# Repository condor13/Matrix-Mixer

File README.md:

# Matrix-Mixer rev.02 - IN PRODUCTION!

Welcome to the Matrix-Mixer wiki! Matrix mixer is a device that routes multiple input audio signals to multiple outputs.
It employs level controls to determine how much of each input is going to each output. The number of individual controls 
is the number of inputs witch is six multiplied by the number of outputs witch is six so (complex math) 36 controls.
It outputs mono, converts synth level signals to pro line level (+4dBu). LED`s for input clipping.

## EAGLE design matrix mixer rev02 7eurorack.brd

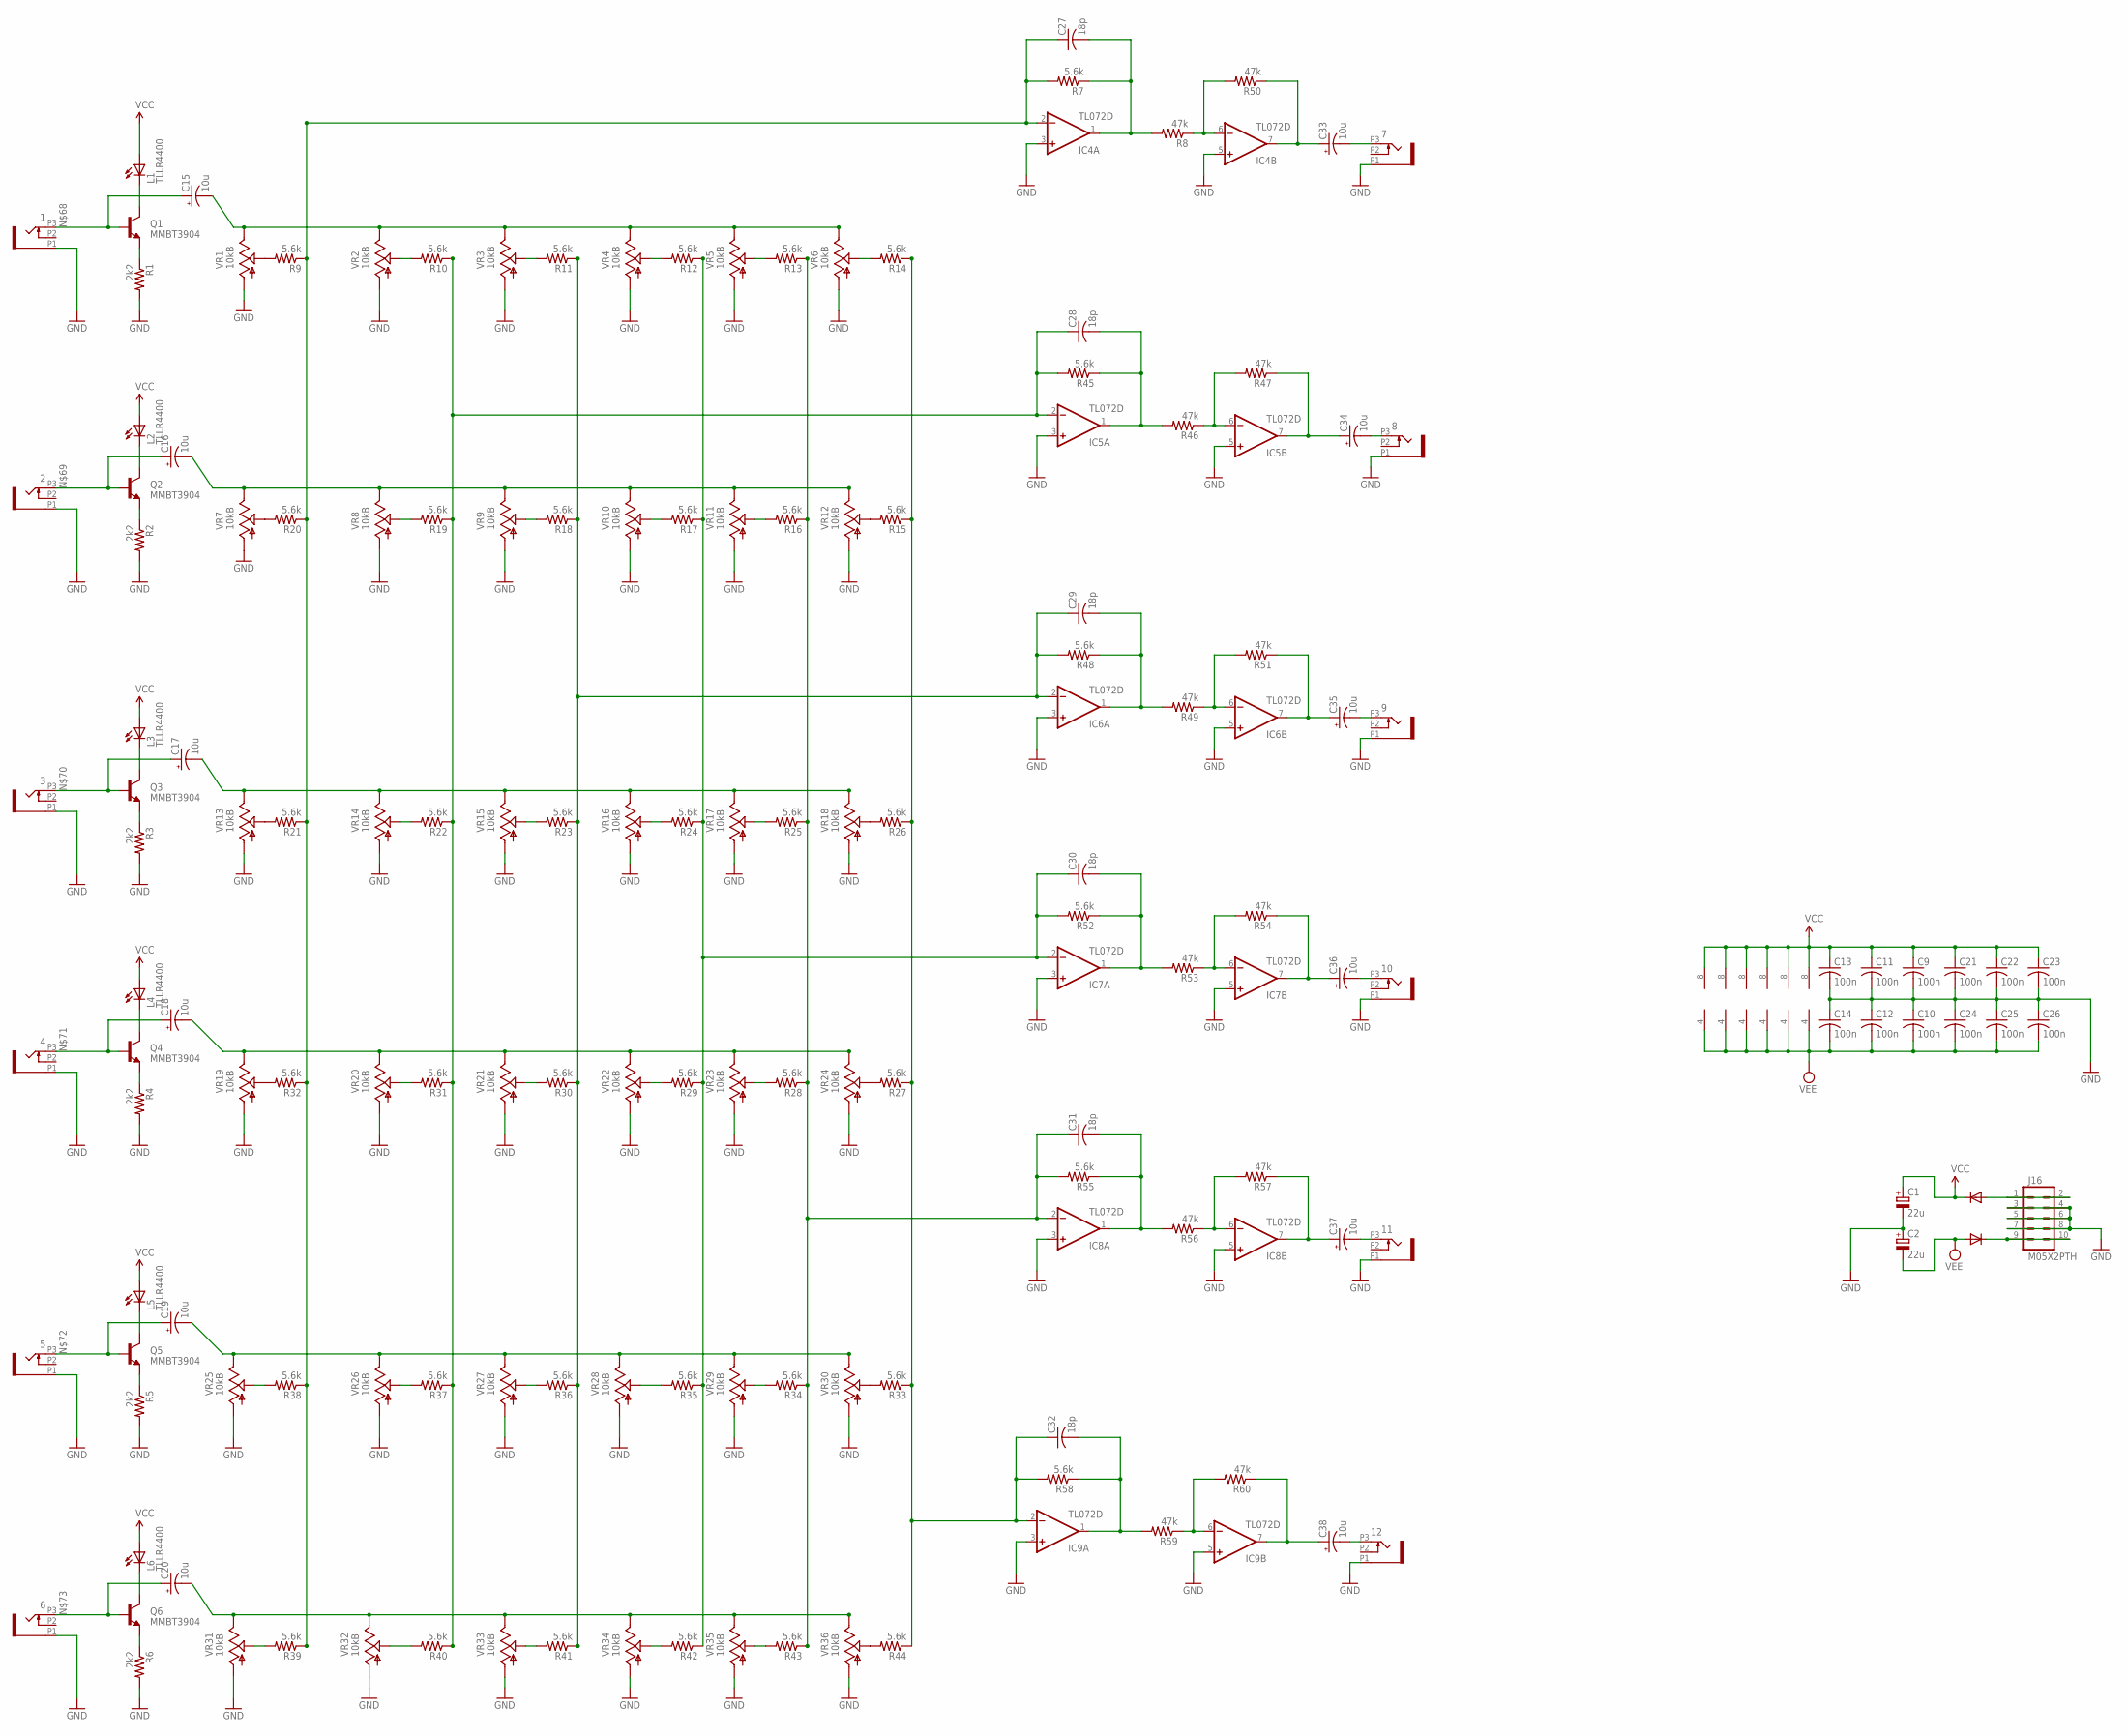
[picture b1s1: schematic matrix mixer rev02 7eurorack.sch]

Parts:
1, 2, 3, 4, 5, 6, 7, 8, 9, 10, 11, 12: PJ301_THONKICONN6; WQP_PJ_301M6
C1, C2: 22u; PANASONIC_D
C9, C10, C11, C12, C13, C14, C21, C22, C23, C24, C25, C26: 100n; C0603
C15, C16, C17, C18, C19, C20, C33, C34, C35, C36, C37, C38: 10u; PANASONIC_B
C27, C28, C29, C30, C31, C32: 18p; C0603
D1, D2: 1N5819HW; SOD123
IC4, IC5, IC6, IC7, IC8, IC9: TL072D; SO08
J16: M05X2PTH; AVR_ICSP
L1, L2, L3, L4, L5, L6: TLLR4400; LED3MM
Q1, Q2, Q3, Q4, Q5, Q6: MMBT3904; SOT23-BEC
R1, R2, R3, R4, R5, R6: 2k2; R0603
R7, R9, R10, R11, R12, R13, R14, R15, R16, R17, R18, R19, R20, R21, R22, R23, R24, R25, R26, R27, R28, R29, R30, R31, R32, R33, R34, R35, R36, R37, R38, R39, R40, R41, R42, R43, R44, R45, R48, R52, R55, R58: 5.6k; R0603
R8, R46, R47, R49, R50, R51, R53, R54, R56, R57, R59, R60: 47k; R0603
VR1, VR2, VR3, VR4, VR5, VR6, VR7, VR8, VR9, VR10, VR11, VR12, VR13, VR14, VR15, VR16, VR17, VR18, VR19, VR20, VR21, VR22, VR23, VR24, VR25, VR26, VR27, VR28, VR29, VR30, VR31, VR32, VR33, VR34, VR35, VR36: 10kB; ALPS_POT_VERTICAL_PS

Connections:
GND: 1.P1 (1), 2.P1 (1), 3.P1 (1), 4.P1 (1), 5.P1 (1), 6.P1 (1), 7.P1 (1), 8.P1 (1), 9.P1 (1), 10.P1 (1), 11.P1 (1), 12.P1 (1), C1.-, C2.+, C9.2, C10.1, C11.2, C12.1, C13.2, C14.1, C21.2, C22.2, C23.2, C24.1, C25.1, C26.1, IC4.3 (+IN), IC4.5 (+IN), IC5.3 (+IN), IC5.5 (+IN), IC6.3 (+IN), IC6.5 (+IN), IC7.3 (+IN), IC7.5 (+IN), IC8.3 (+IN), IC8.5 (+IN), IC9.3 (+IN), IC9.5 (+IN), J16.3, J16.4, J16.5, J16.6, J16.7, J16.8, R1.2, R2.2, R3.2, R4.2, R5.2, R6.2, VR1.P$3 (A), VR2.P$3 (A), VR3.P$3 (A), VR4.P$3 (A), VR5.P$3 (A), VR6.P$3 (A), VR7.P$3 (A), VR8.P$3 (A), VR9.P$3 (A), VR10.P$3 (A), VR11.P$3 (A), VR12.P$3 (A), VR13.P$3 (A), VR14.P$3 (A), VR15.P$3 (A), VR16.P$3 (A), VR17.P$3 (A), VR18.P$3 (A), VR19.P$3 (A), VR20.P$3 (A), VR21.P$3 (A), VR22.P$3 (A), VR23.P$3 (A), VR24.P$3 (A), VR25.P$3 (A), VR26.P$3 (A), VR27.P$3 (A), VR28.P$3 (A), VR29.P$3 (A), VR30.P$3 (A), VR31.P$3 (A), VR32.P$3 (A), VR33.P$3 (A), VR34.P$3 (A), VR35.P$3 (A), VR36.P$3 (A)
INPUT_1: C15.-, VR1.P$1 (E), VR2.P$1 (E), VR3.P$1 (E), VR4.P$1 (E), VR5.P$1 (E), VR6.P$1 (E)
INPUT_2: C16.-, VR7.P$1 (E), VR8.P$1 (E), VR9.P$1 (E), VR10.P$1 (E), VR11.P$1 (E), VR12.P$1 (E)
INPUT_3: C17.-, VR13.P$1 (E), VR14.P$1 (E), VR15.P$1 (E), VR16.P$1 (E), VR17.P$1 (E), VR18.P$1 (E)
INPUT_4: C18.-, VR19.P$1 (E), VR20.P$1 (E), VR21.P$1 (E), VR22.P$1 (E), VR23.P$1 (E), VR24.P$1 (E)
INPUT_5: C19.-, VR25.P$1 (E), VR26.P$1 (E), VR27.P$1 (E), VR28.P$1 (E), VR29.P$1 (E), VR30.P$1 (E)
INPUT_6: C20.-, VR31.P$1 (E), VR32.P$1 (E), VR33.P$1 (E), VR34.P$1 (E), VR35.P$1 (E), VR36.P$1 (E)
unnamed: R9.2, VR1.P$2 (S)
unnamed: Q2.E, R2.1
unnamed: Q1.E, R1.1
unnamed: R10.2, VR2.P$2 (S)
unnamed: R11.2, VR3.P$2 (S)
unnamed: 12.P3 (3), C38.-
unnamed: L2.K (C), Q2.C
unnamed: L1.K (C), Q1.C
unnamed: R12.2, VR4.P$2 (S)
unnamed: R13.2, VR5.P$2 (S)
unnamed: R14.2, VR6.P$2 (S)
unnamed: L4.K (C), Q4.C
unnamed: R15.2, VR12.P$2 (S)
unnamed: R16.2, VR11.P$2 (S)
unnamed: L3.K (C), Q3.C
unnamed: R17.2, VR10.P$2 (S)
unnamed: R18.2, VR9.P$2 (S)
unnamed: R19.2, VR8.P$2 (S)
unnamed: R20.2, VR7.P$2 (S)
unnamed: Q4.E, R4.1
unnamed: R21.2, VR13.P$2 (S)
unnamed: R22.2, VR14.P$2 (S)
unnamed: R23.2, VR15.P$2 (S)
unnamed: R24.2, VR16.P$2 (S)
unnamed: R25.2, VR17.P$2 (S)
unnamed: R26.2, VR18.P$2 (S)
unnamed: Q3.E, R3.1
unnamed: R27.2, VR24.P$2 (S)
unnamed: L6.K (C), Q6.C
unnamed: L5.K (C), Q5.C
unnamed: Q6.E, R6.1
unnamed: Q5.E, R5.1
unnamed: 11.P3 (3), C37.-
unnamed: 10.P3 (3), C36.-
unnamed: 9.P3 (3), C35.-
unnamed: 8.P3 (3), C34.-
unnamed: 7.P3 (3), C33.-
unnamed: R28.2, VR23.P$2 (S)
unnamed: R29.2, VR22.P$2 (S)
unnamed: R30.2, VR21.P$2 (S)
unnamed: R31.2, VR20.P$2 (S)
unnamed: R32.2, VR19.P$2 (S)
unnamed: R33.2, VR30.P$2 (S)
unnamed: D1.A, J16.1, J16.2
unnamed: R34.2, VR29.P$2 (S)
unnamed: D2.C, J16.9, J16.10
unnamed: R35.2, VR28.P$2 (S)
unnamed: R36.2, VR27.P$2 (S)
unnamed: R37.2, VR26.P$2 (S)
unnamed: R38.2, VR25.P$2 (S)
unnamed: R39.2, VR31.P$2 (S)
unnamed: R40.2, VR32.P$2 (S)
unnamed: R41.2, VR33.P$2 (S)
unnamed: R42.2, VR34.P$2 (S)
unnamed: R43.2, VR35.P$2 (S)
unnamed: R44.2, VR36.P$2 (S)
unnamed: C27.1, IC4.2 (-IN), R7.2, R9.1, R20.1, R21.1, R32.1, R38.1, R39.1
unnamed: C28.1, IC5.2 (-IN), R10.1, R19.1, R22.1, R31.1, R37.1, R40.1, R45.2
unnamed: C29.1, IC6.2 (-IN), R11.1, R18.1, R23.1, R30.1, R36.1, R41.1, R48.2
unnamed: C30.1, IC7.2 (-IN), R12.1, R17.1, R24.1, R29.1, R35.1, R42.1, R52.2
unnamed: C31.1, IC8.2 (-IN), R13.1, R16.1, R25.1, R28.1, R34.1, R43.1, R55.2
unnamed: C32.1, IC9.2 (-IN), R14.1, R15.1, R26.1, R27.1, R33.1, R44.1, R58.2
unnamed: 1.P3 (3), C15.+, Q1.B
unnamed: 2.P3 (3), C16.+, Q2.B
unnamed: 3.P3 (3), C17.+, Q3.B
unnamed: 4.P3 (3), C18.+, Q4.B
unnamed: 5.P3 (3), C19.+, Q5.B
unnamed: 6.P3 (3), C20.+, Q6.B
unnamed: C27.2, IC4.1 (OUT), R7.1, R8.2
unnamed: IC4.6 (-IN), R8.1, R50.2
unnamed: C33.+, IC4.7 (OUT), R50.1
unnamed: C28.2, IC5.1 (OUT), R45.1, R46.2
unnamed: IC5.6 (-IN), R46.1, R47.2
unnamed: C34.+, IC5.7 (OUT), R47.1
unnamed: C29.2, IC6.1 (OUT), R48.1, R49.2
unnamed: IC6.6 (-IN), R49.1, R51.2
unnamed: C35.+, IC6.7 (OUT), R51.1
unnamed: C30.2, IC7.1 (OUT), R52.1, R53.2
unnamed: IC7.6 (-IN), R53.1, R54.2
unnamed: C36.+, IC7.7 (OUT), R54.1
unnamed: C31.2, IC8.1 (OUT), R55.1, R56.2
unnamed: IC8.6 (-IN), R56.1, R57.2
unnamed: C37.+, IC8.7 (OUT), R57.1
unnamed: C32.2, IC9.1 (OUT), R58.1, R59.2
unnamed: IC9.6 (-IN), R59.1, R60.2
unnamed: C38.+, IC9.7 (OUT), R60.1
VCC: C1.+, C9.1, C11.1, C13.1, C21.1, C22.1, C23.1, D1.C, IC4.8 (V+), IC5.8 (V+), IC6.8 (V+), IC7.8 (V+), IC8.8 (V+), IC9.8 (V+), L1.A, L2.A, L3.A, L4.A, L5.A, L6.A
VEE: C2.-, C10.2, C12.2, C14.2, C24.2, C25.2, C26.2, D2.A, IC4.4 (V-), IC5.4 (V-), IC6.4 (V-), IC7.4 (V-), IC8.4 (V-), IC9.4 (V-)

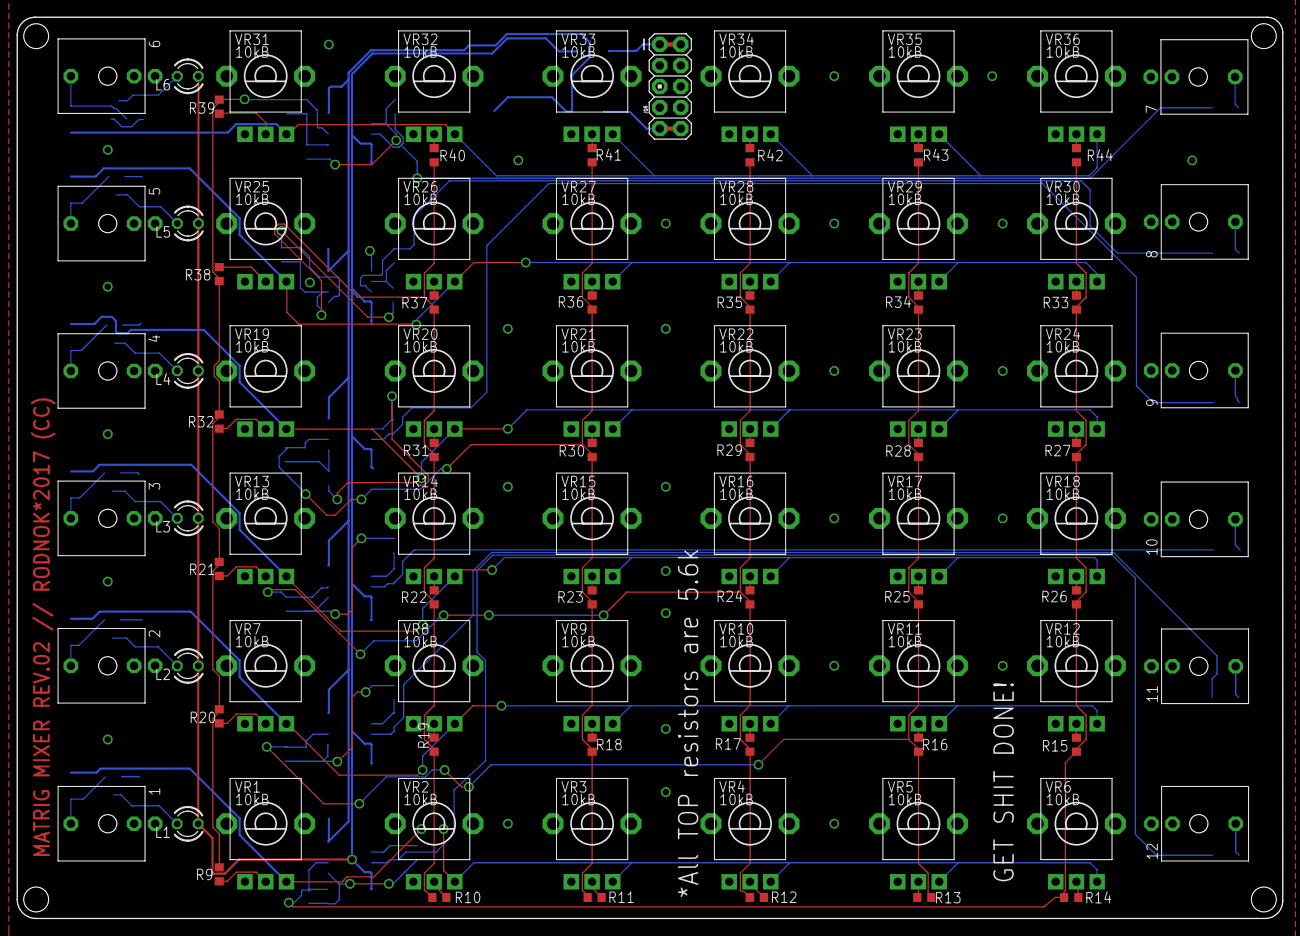
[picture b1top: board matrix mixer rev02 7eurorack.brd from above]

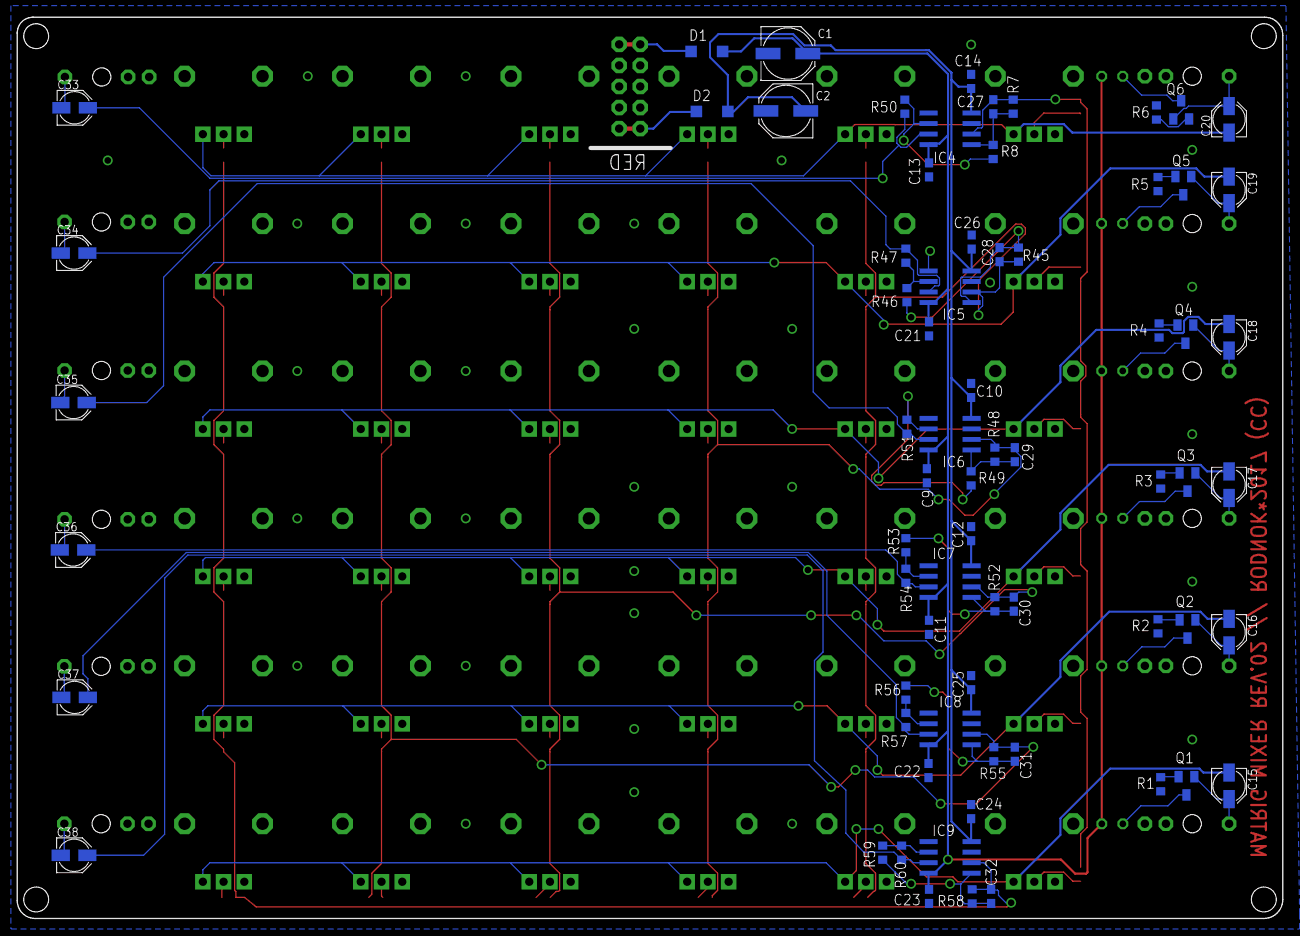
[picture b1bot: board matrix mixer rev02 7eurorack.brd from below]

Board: 2 copper layers, 152.7 x 108.7 mm, 161 parts (70 on the bottom side), 95 nets.

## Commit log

2017-09-29 Add files via upload
    Modfied the board size and via size.
2017-11-24 Rev.02
2017-11-24 rev.02 and Panel
